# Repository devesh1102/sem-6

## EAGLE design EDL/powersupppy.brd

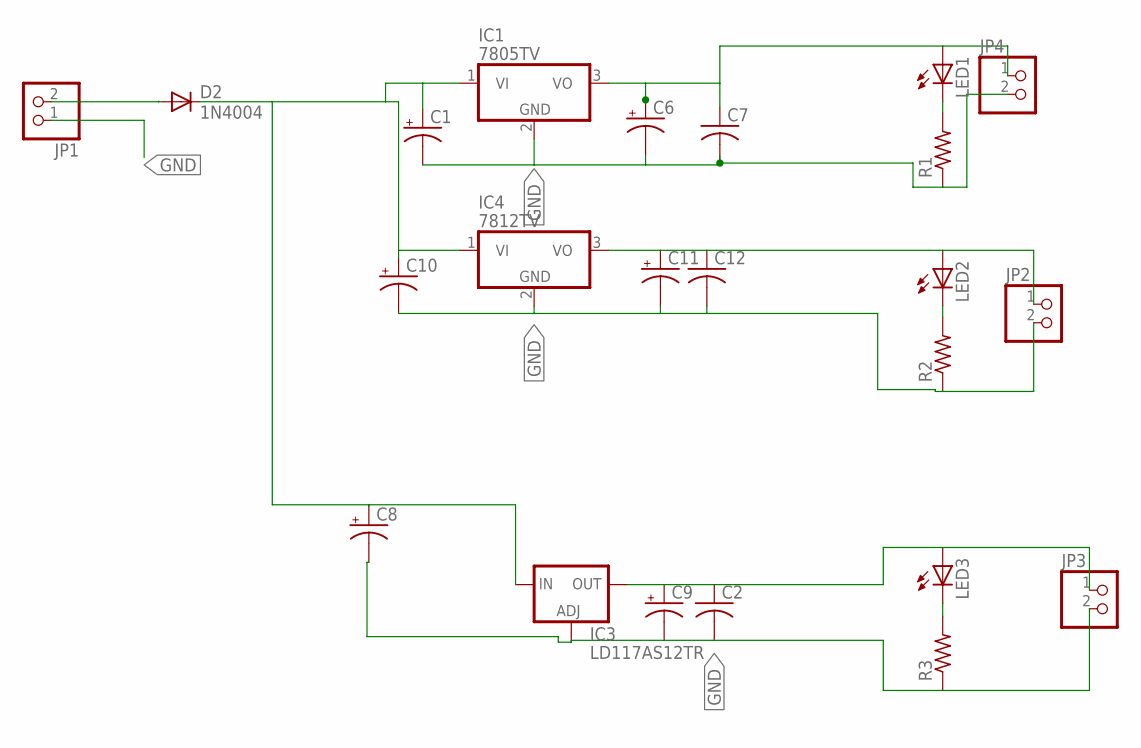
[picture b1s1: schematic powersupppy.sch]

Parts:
C1, C6, C8, C9, C10, C11: CPOL-USE2.5-5; E2,5-5
C2, C7, C12: C-US050-025X075; C050-025X075
D2: 1N4004; DO41-10
IC1: 7805TV; TO220V
IC3: LD117AS12TR; SOT223
IC4: 7812TV; TO220V
JP1, JP2, JP3, JP4: PINHD-1X2; 1X02
LED1, LED2, LED3: LED3MM
R1, R2: R-US_0207/10; 0207/10
R3: R-US_R1206; R1206

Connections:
GND: C1.-, C2.2, C6.-, C7.2, C8.-, C9.-, C10.-, C11.-, C12.2, IC1.2 (GND), IC3.1 (ADJ), IC4.2 (GND), JP1.1, JP2.2, JP3.2, JP4.2, R1.1, R2.1, R3.1
unnamed: D2.A, JP1.2
unnamed: C1.+, C8.+, C10.+, D2.C, IC1.1 (VI), IC3.3 (IN), IC4.1 (VI)
unnamed: C6.+, C7.1, IC1.3 (VO), JP4.1, LED1.A
unnamed: LED1.K (C), R1.2
unnamed: C11.+, C12.1, IC4.3 (VO), JP2.1, LED2.A
unnamed: LED2.K (C), R2.2
unnamed: C2.1, C9.+, IC3.4 (OUT), JP3.1, LED3.A
unnamed: LED3.K (C), R3.2

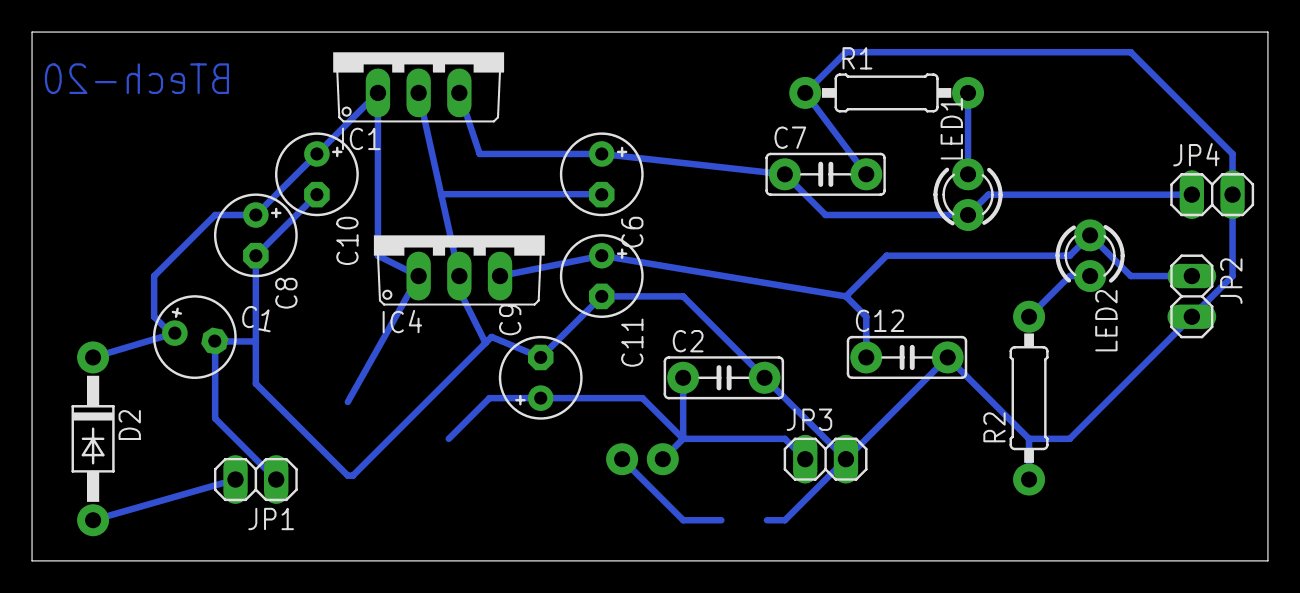
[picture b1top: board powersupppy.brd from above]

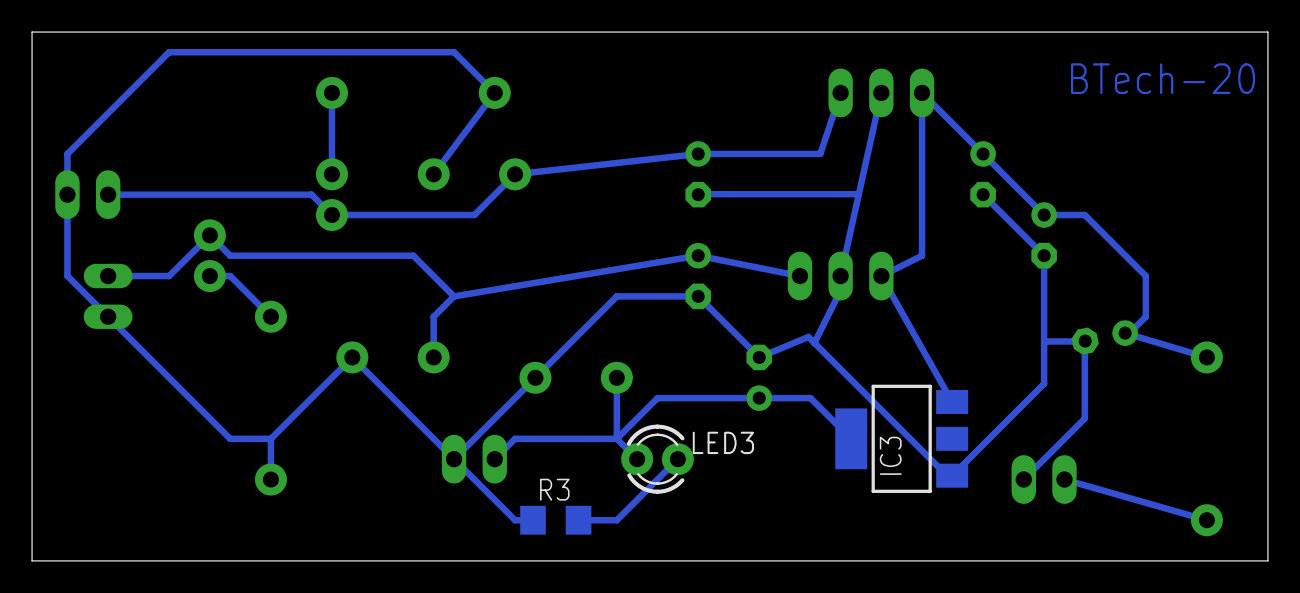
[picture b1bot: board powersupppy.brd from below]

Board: 2 copper layers, 77.1 x 33.0 mm, 23 parts (3 on the bottom side), 9 nets.

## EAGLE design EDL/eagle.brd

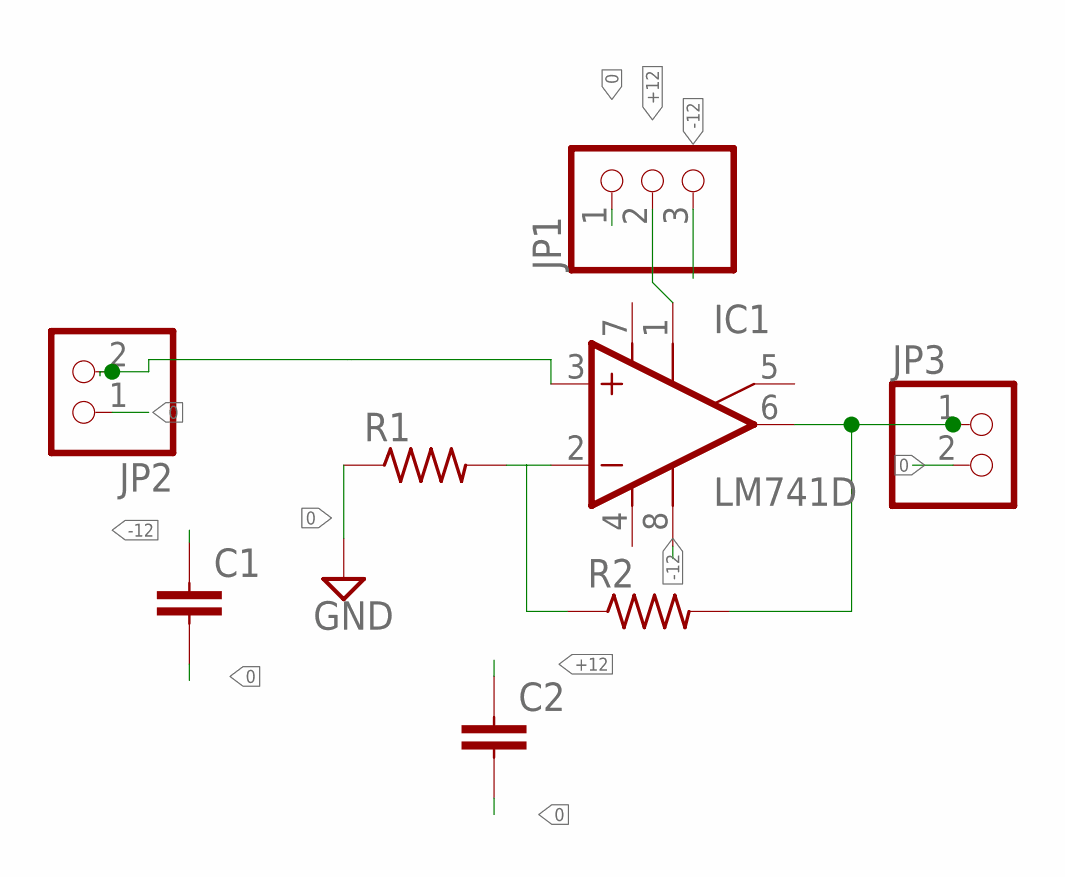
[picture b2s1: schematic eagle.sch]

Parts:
C1, C2: C-EU050-025X075; C050-025X075
IC1: LM741D; SO08
JP1: PINHD-1X3; 1X03
JP2, JP3: PINHD-1X2; 1X02
R1, R2: R-US_0207/10; 0207/10

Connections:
0: C1.2, C2.2, JP1.1, JP2.1, JP3.2, R1.1
+12: C2.1, IC1.1 (ON1), JP1.2
-12: C1.1, IC1.8 (OPT), JP1.3
unnamed: IC1.3 (+IN), JP2.2
unnamed: IC1.2 (-IN), R1.2, R2.1
unnamed: IC1.6 (OUT), JP3.1, R2.2
V+: IC1.7 (V+)
V-: IC1.4 (V-)

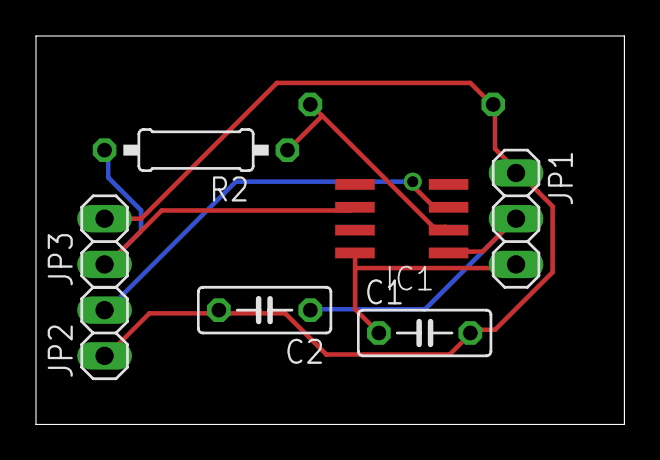
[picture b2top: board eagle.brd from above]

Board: 2 copper layers, 32.7 x 21.6 mm, 8 parts (1 on the bottom side), 6 nets.

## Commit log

2020-12-05 dumping all file
2020-12-05 adding all files after downloading from icloud
